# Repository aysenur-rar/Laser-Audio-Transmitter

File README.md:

# Free-Space Optical (FSO) Audio Transceiver

### Project Overview
This project demonstrates a wireless optical communication system capable of transmitting high-fidelity analog audio signals over a distance of 10+ meters using a collimated laser beam. The system integrates a custom-designed optical lens assembly (simulated in Ansys Zemax) with a Class-A analog modulation circuit (designed in KiCad).

### 📸 Visuals
| PCB Layout | 3D Render |
| :---: | :---: |
|  |  |

### 🚀 Key Features
* **Optical Range:** >10 meters with <2 mrad beam divergence.
* **Modulation Scheme:** Analog Intensity Modulation (IM/DD).
* **Optical Power:** <5mW (Class 3R Safety Compliance).
* **Bandwidth:** 20Hz - 20kHz (Full Audio Spectrum).

### 🛠 Technical Implementation

#### 1. Electronics Design (KiCad)
* **Topology:** Common Emitter Voltage Amplifier with DC Bias network.
* **Bias Point Analysis:** Designed a stable Q-point ($V_{bias} \approx 1.6V$) to maintain the laser diode in its linear region, preventing clipping of the AC audio signal.
* **Current Limiting:** Integrated a calculated emitter degeneration resistor ($33\Omega$) to cap forward current at safe limits (~200mA) while maintaining gain.

#### 2. Optical Design (Ansys Zemax)
* **Objective:** Collimation of a diverging laser diode source to maximize power transfer.
* **Methodology:** Performed RMS Spot Radius optimization on a plano-convex lens system.
* **Result:** Achieved a highly collimated beam with minimal wavefront error.

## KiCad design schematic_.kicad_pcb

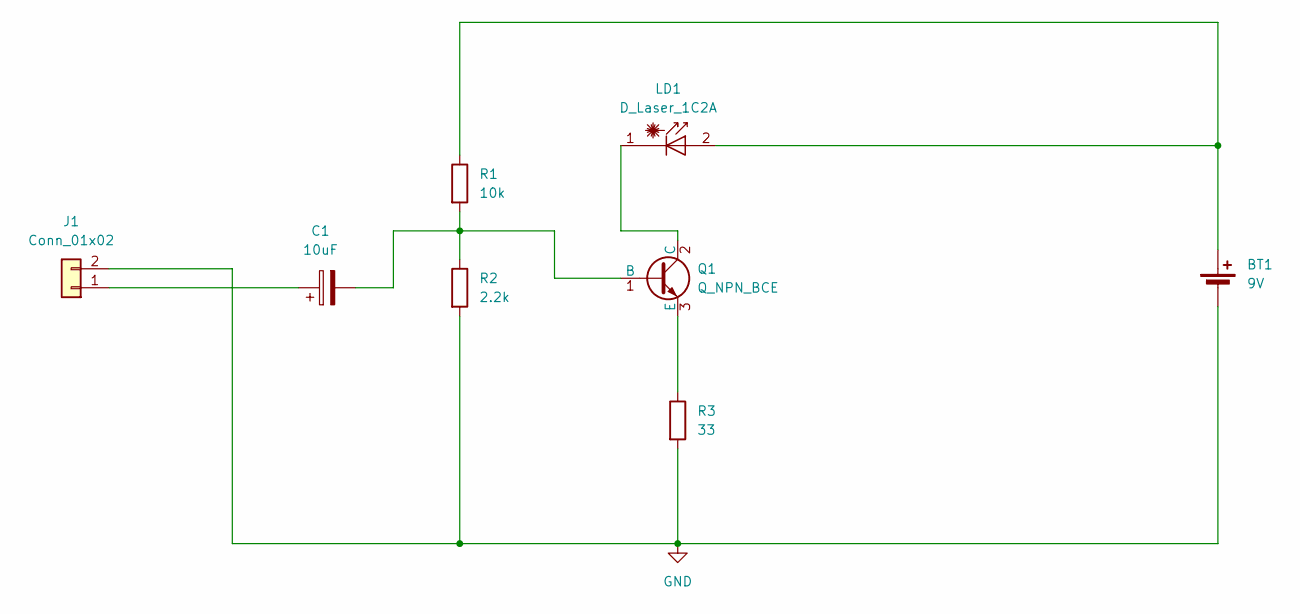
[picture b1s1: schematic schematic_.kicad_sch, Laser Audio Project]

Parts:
BT1: 9V; PinSocket_1x02_P2.54mm_Vertical
C1: 10uF; CP_Radial_D5.0mm_P2.50mm
J1: Conn_01x02; PinHeader_1x02_P2.54mm_Vertical
LD1: D_Laser_1C2A; PinSocket_1x02_P2.54mm_Vertical
Q1: Q_NPN_BCE; TO-92_Inline
R1: 10k; R_Axial_DIN0207_L6.3mm_D2.5mm_P7.62mm_Horizontal
R2: 2.2k; R_Axial_DIN0207_L6.3mm_D2.5mm_P7.62mm_Horizontal
R3: 33; R_Axial_DIN0207_L6.3mm_D2.5mm_P7.62mm_Horizontal

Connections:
GND: BT1.2 (-), J1.2, R2.2, R3.2
unnamed: BT1.1 (+), LD1.2 (A), R1.1
unnamed: C1.1, J1.1
unnamed: LD1.1 (K), Q1.2 (C)
unnamed: C1.2, Q1.1 (B), R1.2, R2.1
unnamed: Q1.3 (E), R3.1

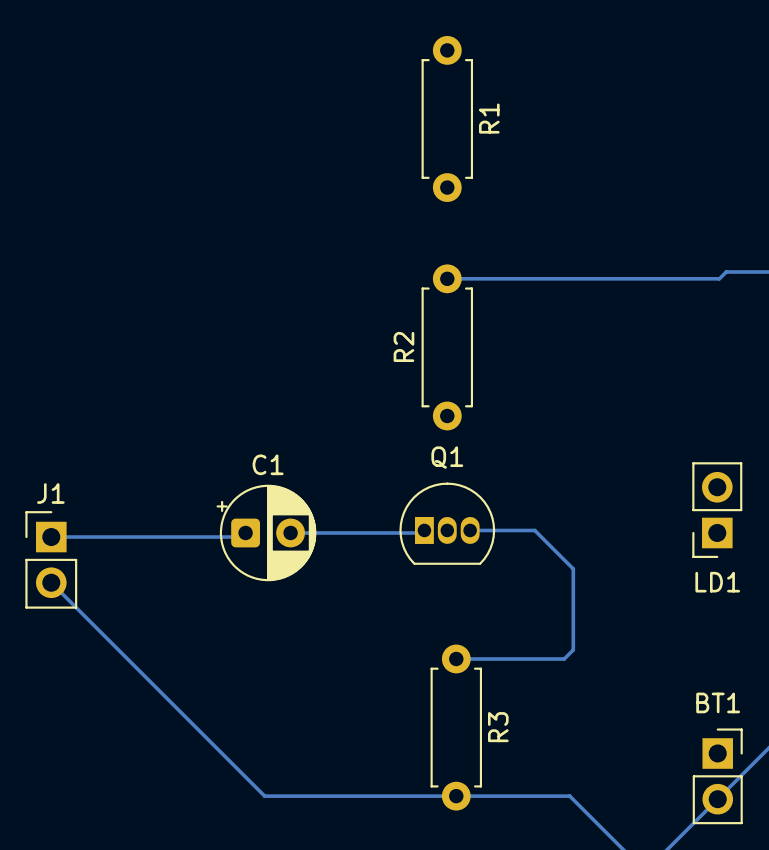
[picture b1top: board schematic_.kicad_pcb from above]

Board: 2 copper layers, 8 parts (0 on the bottom side), 6 nets.

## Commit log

2025-12-01 Initial release of V1 hardware
2025-12-01 README.md
2025-12-01 Added Ansys Zemax optical simulation files
2025-12-01 pcb_layout.png
2025-12-01 3d_render.png
